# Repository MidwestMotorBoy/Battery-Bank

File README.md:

# Monolith

An ultralight 91 Wh USB-C power bank for backpacking: 4S1P 21700 pack, two bidirectional USB-C PD ports designed for 100 W total, TI CC2340 Bluetooth LE MCU.

## Where the project stands (2026-11-13)

Nothing has been built, assembled or bench-tested yet. Every number in this repo is a design or model value, not a measurement.

- **The design is complete on paper:** schematic, board layout, enclosure model with print files, assembly and bring-up procedures, and a parts tracker for the first five packs.
- **The board is the script-built layout on `master`** (Logan's choice on 2026-11-13; details in [The board layout and its predecessor](#the-board-layout-and-its-predecessor)). It passes DRC and was checked by solver, but it has not been reviewed by a person. Its JLC order files were made on 2026-11-14 ([`ORDER-NOTES.md`](hardware/Production/jlc/ORDER-NOTES.md)). The earlier hand-routed layout, approved on 2026-10-30, is history: its order files, reviews and board-specific studies are kept and labelled as such.
- **The enclosure has been through four drop studies and a thermal study**, the last a full 3D explicit drop model (2026-11-11 and 11-12) that added the rail spines under the board. See [Analysis](#analysis).
- **Next:** review the board in KiCad, fix three silkscreen items and order it, print the first cup (it is the fit test: there are no separate fit coupons), weld a pack, bring the board up, and run the drop and thermal tests that the models can only estimate.

Where to read more:

| | |
|---|---|
| [`docs/spec.md`](docs/spec.md) | The single source of truth for every decision (cells, thresholds, enclosure, firmware policy). Where this README and the spec disagree, the spec wins |
| [`hardware/Production/README.md`](hardware/Production/README.md) | The board's dated change log with the reasoning for each part choice |
| [`docs/analysis/`](docs/analysis/README.md) | Model studies: thermal, drop, bumper materials, switching loops, inner copper |
| [`docs/reviews/`](docs/reviews/README.md) | Board and enclosure reviews, with the full review history |
| [`docs/mechanical-design.md`](docs/mechanical-design.md), [`docs/viewer/`](docs/viewer/README.md) | The enclosure and its interactive 3D viewer |
| [`docs/production/`](docs/production/) | Assembly, spot welding, bring-up and gauge training |
| [`ordering/`](ordering/README.md) | What to buy, from where, and its status |

## Design overview

The goal is a hiking power bank that is lighter and better behaved than the off-the-shelf ones: under the 100 Wh carry-on limit, able to charge or run 20 V USB-C PD loads, with a proper fuel gauge and a phone app. The pack is four BAK N21700CX-65E cells (6.5 Ah, 3.5 V nominal) in 4S1P: 91 Wh typical, spot-welded with pure nickel strip and managed by a TI BQ40Z50-R2 gauge/protector with hardware second-level protection (BQ294700 plus a chemical fuse). Each of the two USB-C ports has its own TPS25751 PD controller and BQ25756 bidirectional buck-boost converter, so either port can charge the pack (including from a 5 V solar panel) or source up to 20 V / 5 A, with the pair thermally limited to 100 W; a TPS62933 buck supplies each port's 5 V source rail and a TPS62177 buck supplies the 3.3 V rail. A CC2340R5MODA Bluetooth LE module runs the charge policy, port power sharing and a custom GATT service for an iPhone app. The electronics live on one 43 × 74 mm 6-layer board along one face of the cells, inside an MJF nylon cup closed on five sides and sealed by a bottom cap with one radial O-ring, with TPU bumpers at both ends. There is no metal enclosure: the power stage sheds its heat into the cells through thermal vias and a gap filler.

| | |
|---|---|
| **Energy** | 91 Wh typical, 88.9 Wh minimum (4S1P, 14.0 V, 6.5 Ah, BAK N21700CX-65E cells), under the 100 Wh carry-on limit |
| **Ports** | 2 × USB-C, each bidirectional PD 5–20 V up to 5 A; 100 W total as a burst, then a linear thermal derate to a sustained ~40 W ([policy](docs/firmware/charge-and-thermal-policy.md)) |
| **Gauge / protection** | BQ40Z50-R2 (Impedance Track, SMBus), Infineon BSC007N04LS6 CHG/DSG FETs, 1 mΩ shunt; BQ294700 + chemical fuse as the independent second level |
| **MCU** | TI CC2340R5MODA (Cortex-M0+ Bluetooth LE module with integrated antenna) |
| **Board** | 43.2 × 74.35 mm, 6 layers, 1.6 mm, 2 oz outer / 0.5 oz inner copper, ENIG, filled and capped vias; JLCPCB assembly of F.Cu, B.Cu parts hand-fitted |
| **Enclosure** | MJF PA12 cup and bottom cap (one radial NBR O-ring), PA12 cell carrier and board rails, TPU 95A bumpers; 60.9 × 52.7 × 95.5 mm, about 402.2 g (modelled); IP67 is the target |
| **Tools** | KiCad 10 with Python scripts, TI SimpleLink Low Power F3 SDK, Xcode (app on the `app` branch) |

## Status

**Done**

- **Schematic:** six sheets, 289 footprints. Derived by script from an earlier bench design that went through four schematic reviews, with a netlist check that every surviving pin kept its net. Loss cuts, the BAK 65E cell change, the late part swaps (TVS2200 clone, KEMET T593V bulk caps, 2.0 mm inductors) and the UART_TX debug pin are in. ERC is clean (0 errors).
- **Board layout:** the script-built layout of 2026-11-10 (PR #66, commit `dd34285`), placed and routed by script into the outline the enclosure gives, DRC clean, and ahead of or level with the earlier hand-routed layout on loop inductance, copper loss and via current in the solver comparison. Logan made it the design on 2026-11-13. A whole-project pre-order review on 2026-11-07 found no wiring error in the schematic it implements.
- **Earlier hand-routed layout (history):** placed 2026-10-28, routed and reviewed revision by revision up to rev 12 on 2026-10-30, approved the same day (PR #44). It is the board file at commit `8dd9eb6`; its order files are in [`hardware/Production/retired/jlc-hand-routed/`](hardware/Production/retired/jlc-hand-routed/ORDER-NOTES.md).
- **Mechanical:** parametric cup enclosure with 129 clearance, seal, sealed-pressure and drop load-path checks, all passing, STL print files by material, STEP export and an interactive viewer ([`docs/mechanical-design.md`](docs/mechanical-design.md)). The cup carries the drop loads since 2026-11-03 (edge lands, lips, cradles, spacers) and props the board at mid-span since 2026-11-11 (rail spines).
- **Analysis:** thermal with both ports loaded, four drop studies ending in a full 3D explicit model, a bumper materials study, the inductance of every switching loop, and an inner copper weight study ([Analysis](#analysis)).
- **Cells and pack build:** BAK N21700CX-65E, BSC007N04LS6 protection FETs sized for its short-circuit current ([options](research_notes/protection-fets/options.md)), P20B spot welding with 0.2 × 10 mm pure nickel and wire PACK tails ([welding](docs/production/spot-welding.md), [assembly](docs/production/p0-assembly.md)), Parker GEL 30 gap filler, front-cell NTCs as SMD parts on the board under the gap filler (TH101 / TH104).
- **Firmware policy:** charge current and discharge power as linear ramps on the hottest cell temperature ([policy](docs/firmware/charge-and-thermal-policy.md)); a LaunchPad build of the firmware skeleton and TI's `basic_ble` runs.
- **Ordering:** every part for five packs is in [`ordering/parts-tracker.csv`](ordering/README.md). The two parts LCSC does not stock (TPS25751D, SiZ240DT) were pre-ordered at JLC on 2026-11-07.

**Remaining**

- Review the board in KiCad: it has been checked by DRC, script and solver only.
- Fix the silkscreen items in [`ORDER-NOTES.md`](hardware/Production/jlc/ORDER-NOTES.md) (the title text is off the board edge), rerun `hardware/Production/jlc/make_package.sh` after any board change, and go through the checkout checks there.
- Rerun the board-specific studies for this layout where the margin is small: the 3D drop model (of the four capacitors with the smallest wall margins, three moved by 5 to 13 mm and the fourth turned 90°) and the thermal runs.
- Order the board and the printed parts. The first real cup, cap and core are the fit test.
- Weld the pack, bring up the board and train the gauge ([`docs/production/p0-bringup-and-training.md`](docs/production/p0-bringup-and-training.md)).
- Firmware beyond the skeleton: the P0 pin map, gauge and PD-controller drivers, the TPS25751 patch bundle and its loader, charge policy, power sharing, BLE GATT, MCUboot OTA.
- Tests the models cannot replace: a witness-paint drop test on the first print, the 100 W thermal test, an IP67 dunk test, label ratings.
- Thermal rerun with the 1.6 mm cup walls and the rail spines (the spines take about 12 % of the gap filler's conductance; the thermal study predates them).
- iPhone app (SwiftUI + CoreBluetooth).

## Hardware

### The KiCad project

Everything for the board is in [`hardware/Production/`](hardware/Production/), KiCad 10. The symbol library, footprint library and 3D models are project-local, so the project opens with no extra setup.

| File | What it is |
|---|---|
| `Monolith.kicad_pro` | The project; open this |
| `Monolith.kicad_pcb` | The 6-layer board: the script-built layout (commit `dd34285`). The earlier hand-routed layout is the same file at commit `8dd9eb6` (see below) |
| `Monolith.kicad_sch` | Root sheet. Sub-sheets: `gauge.kicad_sch` (Cells and Gauge), `power.kicad_sch` (3V3 Rail), `mcu.kicad_sch` (MCU), and `usb_port.kicad_sch` used twice (USB Port 1, USB Port 2) |
| `MonolithDev.kicad_sym`, `MonolithDev.pretty/`, `3dmodels/` | Project-local symbol library, footprints and STEP models (wired up by `sym-lib-table` / `fp-lib-table`) |
| `Monolith.kicad_dru` | Custom DRC rules (net-class clearances, keep-outs) |
| `jlc/` | [`ORDER-NOTES.md`](hardware/Production/jlc/ORDER-NOTES.md): the JLCPCB order package for this board (gerber zip, BOM, CPL, hand-solder list, made 2026-11-14 by `make_package.sh`), the PCB options and the checkout checks |
| `retired/jlc-hand-routed/` | History: the complete order package of the hand-routed layout (gerber zip, BOM, CPL, hand-solder list). Not for today's board |
| `tools/` | Python scripts that generated the schematic, stack-up, outline and mechanical keep-outs from the enclosure model ([table](hardware/Production/README.md#tools)) |
| `groundup/` | The tools, passes and solver comparison behind the script-built layout ("ground-up" in that folder's notes; [README](hardware/Production/groundup/README.md)) |
| `README.md` | Dated change log: every part choice and change with its reasoning |

The board outline, peg holes, wire holes and keep-outs come from the enclosure model (`hardware/mechanical/monolith_shell.py`) through `tools/make_board.py`, so mechanical changes go there first. Reference designators follow the sheets: 1xx cells and gauge, 2xx 3V3 rail, 3xx MCU, 4xx port 1, 5xx port 2.

### The board layout and its predecessor

Two layouts of the same schematic exist. On 2026-11-13 Logan chose the script-built one as the design. Both use the same outline, holes, USB-C connectors, wire pads, NTCs, antenna module, bottom-side parts and main inductors, so both fit the same cup; 246 of the 289 footprints have a different position or rotation (234 moved by more than 0.1 mm).

| | Script-built board (the design) | Hand-routed board (history) |
|---|---|---|
| **Where** | `Monolith.kicad_pcb` on `master` (commit `dd34285`, PR #66, 2026-11-10) | `Monolith.kicad_pcb` at commit `8dd9eb6` |
| **How it was made** | Placed and routed by script from the schematic, with a DC and loop-inductance solver in the loop, in two fix passes ([`groundup/`](hardware/Production/groundup/README.md)) | Placed and routed by hand in KiCad |
| **Review** | DRC clean (0 errors, 0 unconnected); compared by solver against the hand-routed board ([`groundup/compare/`](hardware/Production/groundup/compare/README.md)); **not yet reviewed by a person** | Reviewed revision by revision up to rev 12 and a final blocker review on 2026-10-30, approved (PR #44) |
| **Solver comparison (model values)** | Charger hot loops 0.50 to 0.56 nH; gate loops 44 nH in sum; copper loss at 100 W 435 / 358 mW (port 1 / port 2); 5.3 / 5.7 min at 100 W before the derate; 258 mm of signal track in a ground plane | 0.54 to 0.67 nH; 49 nH; 469 / 415 mW; 5.0 / 5.3 min; 34 mm |
| **Order files** | None yet. Gerbers, BOM and CPL are made together after the review ([`jlc/ORDER-NOTES.md`](hardware/Production/jlc/ORDER-NOTES.md)) | Complete set, kept in [`retired/jlc-hand-routed/`](hardware/Production/retired/jlc-hand-routed/ORDER-NOTES.md) |
| **Renders, plots, mechanical board data** | Regenerated from this board on 2026-11-13; all 129 enclosure checks pass with its part positions | In git history (pictures at `401b2ee` and earlier; part meshes kept as `hardware/mechanical/board/monolith_board_handrouted.npz`) |
| **Reviews and studies** | The solver comparison only. The drop and thermal studies have not been rerun for its part positions | Every board review in [`docs/reviews/`](docs/reviews/README.md) and every study in [`docs/analysis/`](docs/analysis/README.md) used this board |

As of 2026-11-13, open PR #68 holds a cleaned-up version of the script-built board (a tidiness pass on 2026-11-11) and would replace the board file on `master` if merged; the pictures can be made again with [`docs/hardware/board_pictures.py`](docs/hardware/board_pictures.py). Never mix files between the two layouts: gerbers made from the board on `master` with the CPL in `retired/jlc-hand-routed/` would place almost every part in the wrong spot.

### Schematics, renders and plots

- [`docs/hardware/monolith-p0-schematic.pdf`](docs/hardware/monolith-p0-schematic.pdf): all six sheets, exported from the current schematic on 2026-11-13. It is the same for both layouts.
- [`docs/hardware/monolith-p0-layers.pdf`](docs/hardware/monolith-p0-layers.pdf): the script-built board, front and back (copper, mask, silk), then every copper layer (F.Cu, In1–In4, B.Cu), one page each, plotted on 2026-11-13 from master's board (`dd34285`).
- A 3D STEP of the whole assembly can be generated with `hardware/mechanical/monolith_step.py`.

#### The board

Raytraced in KiCad 10 (`kicad-cli pcb render`, all 3D models) on 2026-11-13 from the board on `master` (`dd34285`) by [`docs/hardware/board_pictures.py`](docs/hardware/board_pictures.py), which also writes the plots and the layers PDF.

<p align="center"></p>

| Top (F.Cu side, faces the cup wall) | Bottom (B.Cu side, faces the cells) |
|---|---|
|  |  |

<p align="center"></p>

#### Board plots

| Front (F.Cu, mask, silk) | Back (B.Cu, mask, silk, mirrored) |
|---|---|
|  |  |

The USB-C ports are at the top edge of the plots (the right edge of the flat renders), the cell wire holes (PACK−, PACK+ and the Kelvin senses) at the bottom tab, and the two power stages fill the middle: USB1's stage (L401) toward +y and USB2's (L501) toward −y. The bare copper boxes on the back are the gap-filler pads that couple the stages to the cells.

### Per port

- TPS25751D USB-C PD controller, configured from its own M24512 EEPROM (patch-bundle programming notes in [`docs/firmware/tps25751-eeprom-programming.md`](docs/firmware/tps25751-eeprom-programming.md)).
- BQ25756 bidirectional buck-boost, 5 mΩ sense resistors, two SiZ240DT 40 V half-bridges, Coilcraft XGL7030-332 3.3 µH at 500 kHz, and a 9 V gate-drive LDO (TPS7A4101), off by default and enabled through the TPS25751's GPIO6 when the pack is above 10 V. Gate resistors fitted as 0 Ω links with DNP RC snubbers so ringing can be fixed without a respin.
- TPS62933 5 V buck for the port's 5 V source rail; TPD6S300 CC protection (24 V short-to-VBUS, IEC ESD); TVS2200 flat clamp on VBUS.
- Shou Han IP68 right-angle USB-C receptacle, 5 A / 20 V.

### Pack and supervision

- BQ40Z50-R2 with four cell NTCs (the two front ones are SMD parts on the board, TH101 / TH104; the back two are wired to their cans), cell balancing and JEITA; BSC007N04LS6 CHG/DSG FETs; 1 mΩ shunt; BQ294700 per-cell OVP that fires the WSFB1514 chemical fuse independently of the gauge.
- One wire-ORed interrupt line (both PD controllers, gauge BTP) into the MCU; CHG_INH pulled up so a reset, hang or unprogrammed MCU stops charging.
- Idle current about 400 µA (estimate, [budget](docs/devboard/power-budget.md)), with a gauge ship mode for storage.

Datasheets and app notes the design was checked against are in `datasheets/`: [`datasheets/README.md`](datasheets/README.md) maps each file to its part.

### Earlier bench design

`hardware/DevBoard/` and `docs/devboard/` hold the bench "dev board" (rev A8) that P0 was derived from: its four schematic reviews, circuit description and budgets. It was never ordered (P0 is the first build since 2026-10-18) and is kept only as the reviewed reference and history.

## Enclosure

The enclosure is a parametric Python model in [`hardware/mechanical/`](hardware/mechanical/) (`monolith_shell.py`, `monolith_parts.py`, `monolith_cup.py`). The model runs its own 129 checks (clearances against the board's part meshes, an insertion sweep, seal squeeze, sealed pressure, drop load-path gaps and bearing stresses) and writes the print files, the pictures in this README and the viewer. [`docs/mechanical-design.md`](docs/mechanical-design.md) describes the design and its checks.

- **Printed parts:** cup, bottom cap, cell carrier, two board rails and four post spacers in MJF PA12; top and bottom bumpers (one piece each, 30 % gyroid slabs) and the cap pad in FDM TPU 95A. Print files by material: [`hardware/mechanical/stl/`](hardware/mechanical/stl/README.md).
- **Sealing:** one 58 × 54 × 2 mm NBR O-ring between cup and cap, the two USB-C receptacles' own seal rings in the cup's bores, and a 12 mm ePTFE vent patch on the cap under the bottom bumper.
- **What holds the core:** the cup carries the loads. Edge lands and lips hold the board's long edges, cradles hold the front cells, the rails ride on the front cans and prop the board at mid-span with a spine across the gap-filler zone, and the cap's feet and overtravel posts catch the core in a cap-end drop.
- **Interactive 3D viewer:** [`docs/viewer/`](docs/viewer/README.md) (parts on and off, section cuts).
- **Assembly:** [`docs/production/p0-assembly.md`](docs/production/p0-assembly.md), with the step pictures in `hardware/mechanical/assembly_steps/`.
- **Label:** the wrap label artwork and print file are in [`hardware/label/`](hardware/label/README.md).

## Analysis

Model studies of the whole pack, each in its own folder under [`docs/analysis/`](docs/analysis/README.md) with the scripts, the numbers as JSON and every figure. Every study was run on the earlier hand-routed board (its copper and its part positions) and the cup as it was on the study's date; none has been rerun for the script-built board that is now the design. The enclosure findings carry over, because the cup, the outline and the parts the cup keys on are the same. The board-specific numbers (copper loss, loop inductance, the parts next to the rail spines in the drop model) describe the hand-routed layout; where the solver comparison in [`groundup/compare/`](hardware/Production/groundup/compare/README.md) has the same number for the script-built board, it is given. Each README opens with a status block that says which geometry it ran on and what became of each finding. Every number is a model value until the bench tests.

| Study | Date | What it answered |
|---|---|---|
| [Thermal, 25 W + 20 W](#thermal-usb1-at-25-w-and-usb2-at-20-w-together) | 2026-10-31 | Both ports loaded from full to empty at 25, 35 and 40 °C |
| [Drop, six poses](#drop-1-m-onto-concrete) | 2026-10-31 | First 1 m drop model; three housing fixes |
| [Bumper materials](#bumper-materials-and-structure) | 2026-11-01, 11-05 | Elastic resins and engineered slabs against FDM TPU |
| [Drop with part-to-part contact](#drop-1-m-onto-concrete) | 2026-11-04, 11-05 | Loads and stress in every part; cup fixes |
| [Inner copper weight](#inner-copper-weight) | 2026-11-05 | 0.5, 1 or 2 oz inner layers |
| [Switching loops](#switching-loop-inductance) | 2026-11-06 | Inductance and ringing of every hot loop and gate loop |
| [Drop in 3D](#drop-1-m-onto-concrete) | 2026-11-11, 11-12 | Full explicit model of the back-face drop; rail spines |

### Thermal: USB1 at 25 W and USB2 at 20 W together

[`docs/analysis/2026-10-31-thermal-25w-20w/`](docs/analysis/2026-10-31-thermal-25w-20w/README.md). Both ports deliver from full to empty (45 W, USB1 at 15 V, USB2 at 9 V) in the 3D pack model ([`research_notes/Pack thermal BAK 65E/`](research_notes/Pack%20thermal%20BAK%2065E/README.md)) with the hand-routed board's copper losses and the firmware derate in the loop.

- **At 25 °C** the pack runs the whole battery at 45 W (118 min, 88.4 Wh) and cuts to 40 W only for the last 3 minutes. The hottest board part peaks at 51 °C, the hottest point in any cell at 45.7 °C, the outside at 46.6 °C.
- **At 35 °C** the derate starts at 20 min and settles at 30 W (USB1 down to 10 W, USB2 kept at 20 W); the hottest part reaches 56 °C and the cells 51 °C. At 40 °C USB1 is cut to 0 W for most of the run.
- **Heat** at 45 W is 2.4 W: 0.8 W in the USB1 stage, 1.0 W in the USB2 stage, 0.5 W in the cells. The 6-layer board keeps itself within 3.6 K end to end.
- Even with the derate switched off at 35 °C (a firmware failure) the cells stop at 55.4 °C, under their 60 °C discharge limit.
- **Not rerun since.** The model's cup has 1.2 mm side walls and no rail spines. The cup now has 1.6 mm walls, and the spines cross the gap-filler zone and take about 12 % of its conductance, so these temperatures are probably slightly optimistic. The copper losses are the hand-routed board's. For the script-built board only the 100 W burst was run, in the solver comparison: 5.3 / 5.7 min before the derate (port 1 / port 2) against 5.0 / 5.3, with the hottest part at 58.1 / 58.9 °C against 59.4 / 60.2 °C.

<p align="center"><sub>The board under the temperatures above is the <b>hand-routed</b> board this study ran on (silk "REV 1.0 10/30/26"), not the script-built board on <code>master</code>. For the current board see <a href="#the-board">The board</a>.</sub></p>

### Inner copper weight

[`docs/analysis/2026-11-05-inner-copper/`](docs/analysis/2026-11-05-inner-copper/README.md). The board is specified with 2 oz outer and 0.5 oz inner copper. This study solved the hand-routed board's power-path resistance and reran the 100 W burst with 1 oz and 2 oz inner layers. The script-built board has the same stack-up; the study has not been repeated on its copper.

| Inner copper | Path resistance, port 1 / port 2 | Port 1 copper loss at 100 W | Minutes at 100 W before the derate, port 1 / port 2 | Hottest part, port 1 / port 2 |
|---|---|---|---|---|
| 0.5 oz (as specified) | 8.63 / 7.50 mΩ | 0.29 W | 5.0 / 5.33 | 59.4 / 60.2 °C |
| 1 oz | 6.95 / 5.75 mΩ | 0.24 W | 5.33 / 5.67 | 57.2 / 57.9 °C |
| 2 oz | 5.96 / 4.68 mΩ | 0.20 W | 5.83 / 6.0 | 54.9 / 55.3 °C |

The gain is almost all heat spreading, not lower I²R: the outer layers carry the high-current copper already. The extra mass is about 1.4 g at 1 oz and about 4 g at 2 oz. 1 oz inner was recommended if JLC's price difference is small; it has not been decided, and the board stays 2 oz / 0.5 oz until it is.

### Drop: 1 m onto concrete

Three models of increasing depth, each built because the one before could not answer the next question. All are for a 1 m drop at 4.43 m/s onto a rigid floor.

1. **Six poses, lumped** ([`2026-10-31-drop-1m/`](docs/analysis/2026-10-31-drop-1m/README.md)). The bumpers' crush law, a finite-element stiffness of the cup and its contents, and a plate model of the board, for a flat drop on each end, the board face, a narrow side, and a corner at each end. It found the 20 % gyroid port-end slab bottoming out (2685 g on the cells and board) and led to three fixes (PR #50): the bumper slabs at **30 % gyroid**, the two M2 screw heads **counterbored 0.8 mm** so they sit below the bumper band, and **pockets in the board-face wall** over the two inductors.
2. **Contact between every moving part** ([`2026-11-04-drop-stress/`](docs/analysis/2026-11-04-drop-stress/README.md)). Each moving part is its own body with contacts to its neighbours, finite-element compliance and stress per part, and the board as a plate on one-sided supports. It gives part loads and stresses for the five flat drops (edges and corners are not usable in this model). It led to the 2026-11-05 cup fixes (PR #64): bottom rail tongues set back, larger cap overtravel posts plus a fifth, and cradle reliefs under two bulk capacitors. It also showed about 8,000 µε in the board in the back-face and board-face drops, which is what the 3D study took up.
3. **Full 3D explicit model of the back-face drop** ([`2026-11-11-drop-3d/`](docs/analysis/2026-11-11-drop-3d/README.md)). OpenCourant, about 900k nodes, quadratic tetrahedra for the nylon and TPU parts, for the worst pose of the lumped studies: flat onto the back (cell) face, where the board's own inertia bends it toward the cells and then swings it into the board-face wall on the rebound. On the cup as it was before this study the board bent across its middle (about 5,000 µε in a full-width band) and the rebound pushed several F.Cu capacitors and inductors into the wall. The fixes (PR #69): **rail spines** that prop the board at mid-span (one clip-on rail per side, its bottom and top blocks joined across the gap-filler zone), ribs on the cup under the board's long edges, 1.5 mm of travel past the bottom rail tongue tips so the rails ride on the front cans, and 0.7 mm inductor pockets. Run 9 checked the merged geometry: board strain 3,089 µε at the 99th percentile and 4,022 µε peak, no F.Cu part reaches the wall, and the tongue tips stop 0.12 mm short. The cap overtravel posts yielded at their sharp top rims, so their tops now have a 0.3 mm chamfer (PR #70, not rerun).

Where each pose stands today, from the newest model that covers it:

| Pose | Newest result | State |
|---|---|---|
| Flat on the port end | 572 g on the cells and board, slab crush 2.6 of 6 mm (lumped, 30 % slab); every part under 7 MPa (contact model) | Fixed by the 30 % slab |
| Flat on the cap end | 1182 g (lumped); overtravel posts 42 MPa, was 107 MPa (contact model) | Open: about 280 N on each bottom rail tongue, and about 1.15 kN on the two M2 screws in the rebound (a lumped estimate) |
| Flat on the back (cell) face | Board 3,089 µε p99, 4,022 µε peak; closest F.Cu part 0.02 mm from the wall (3D, run 9) | Mid-span bending fixed by the rail spines. Open: about 4,000 µε on the board's long edges where the spines end, local yield in the carrier webs, and capacitor margins below the model's resolution |
| Flat on the board face | Board 7,800 µε p99, C434 / C531 0.06 mm from the wall (contact model) | Open. Not rerun since the rail spines and not run in 3D |
| Flat on a narrow side | 4013 g (lumped); cup wall 178 MPa and cradles 143 MPa on a coarse mesh (contact model) | Open: the bottom bumper band is only 1 mm of solid TPU on this side |
| Corners | 2611 g port end, 1550 g cap end (lumped) | No usable stress result in any of the three models |

The lumped g values are from the 2026-10-31 rerun on the 399.6 g cup, before the lands, cradles and spines were added; they have not been rerun on today's 402.2 g cup. The gap filler is carried as mass only: a sensitivity bracket in the contact study suggests it could cut the back-face strain by about 18 % but could also drag parts toward the wall on the rebound. A **witness-paint drop test on the first print** is the planned check for the open items.

The part names and part-to-wall gaps in this table are for the hand-routed board. The script-built board keeps the parts the cup keys on (L401 / L501, the bulk capacitors, the NTCs, the USB-C connectors, the antenna module, the holes), and it passes the model's static clearance checks, but the four capacitors with the smallest margins are not where the studies had them: C434 and C524 moved about 13 mm and C420 about 5 mm; C531 moved 0.4 mm and turned 90°. The margins of 0.02 to 0.06 mm therefore say nothing about the new layout until the contact and 3D models are rerun with its part positions.

### Bumper materials and structure

[`docs/analysis/2026-11-01-bumper-materials/`](docs/analysis/2026-11-01-bumper-materials/README.md). The 2026-10-31 drop model rerun with other materials and slab structures. Analysis only: the design keeps FDM TPU 95A bumpers with 30 % gyroid slabs.

- **Formlabs elastic resins** in the same 6 mm port-end slab give 1,888 to 3,362 g against 572 g for the TPU slab. Flexible 80A V2 needs a 10 mm slab to match, and Flexible 50A never gets below about 1,270 g.
- **PEBA 85A** (studied on 2026-10-31, in the drop study's folder) is 10 to 20 % gentler in the bands but bottoms out worse at the port end, so TPU stays.
- **An engineered slab** does better than a softer material: a vertical-wall honeycomb in TPU 95A at 15 to 17 % gives 397 to 557 g at 1 m with about half the slab mass of today's gyroid (4.6 to 5.3 g against 9.3 g). It has not been adopted in the model.
- **A Flexible 50A cap pad** would hold its preload after heat far better than TPU (compression set 3.1 % against 90 % at 70 °C). It is an idea only.

### Switching-loop inductance

[`docs/analysis/2026-11-06-loop-area/`](docs/analysis/2026-11-06-loop-area/README.md). A 3D partial-inductance solve on the hand-routed board's real copper for every hot loop (the four BQ25756 half-bridge legs, the two 5 V bucks, the 3V3 buck) and the eight gate-drive loops, with ringing estimates.

- **Hot loops:** 0.53 to 0.66 nH on the BQ25756 legs, 0.54 and 0.60 nH on the 5 V bucks, 1.39 nH on the 3V3 buck. The 0402 capacitor next to each FET carries 58 to 68 % of the edge current.
- **Ringing:** the BQ25756 switch nodes ring at about 395 to 425 MHz with an expected peak of 18.8 to 22.4 V; the worst-case bound with an instant edge is 32 to 33 V against the FETs' 40 V rating.
- **Gate loops:** 2.9 to 9.2 nH. The tightest margin is the low-side Miller bounce, about 0.46 V against a 1.1 V minimum threshold.
- **No loop needs a fix.** Two optional tweaks are listed in the study. These numbers are for the hand-routed board.
- **Script-built board:** the same solver steered and checked the new layout ([`groundup/compare/`](hardware/Production/groundup/compare/README.md)). Its four charger hot loops are 0.50 to 0.56 nH, the three small bucks 0.30 to 1.22 nH, and the eight gate loops 3.3 to 8.0 nH, 44 nH in sum. That comparison re-solved the hand-routed board with its own ground setting and got 0.54 to 0.67 nH, 0.53 to 1.40 nH and 49 nH in sum, so compare within one run, not across the two. The ringing estimates were not redone for the script-built board.

### Reviews

Board and enclosure reviews are in [`docs/reviews/`](docs/reviews/README.md), with a table of the whole review history. The board-layout reviews are history: they reviewed the hand-routed layout, and the script-built board has had no review by a person yet. The routed-board review of 2026-10-30 has the copper resistance of every power path and the current-sense tap checks of that layout (its fix list was closed in the later revisions that day), and its solver tools are the ones the script-built layout was checked with. The schematic findings of the reviews apply to both layouts. The mouth-band review (2026-10-31) and the rail-retention review (2026-11-03) are the enclosure decisions behind the thick cup mouth and the cup-carried drop loads.

## Firmware

`firmware/` targets the CC2340R5MODA with TI's SimpleLink Low Power F3 SDK. Until a board exists it runs on the LP-EM-CC2340R53 LaunchPad, which has the same silicon and memory. The firmware has not changed since 2026-10-29.

- **Toolchain:** TI Arm Clang 5.1.1.LTS, SysConfig 1.26.4 and `gmake` from Code Composer Studio 21.0.1, the LPF3 SDK 9.23.00.27, and UniFlash 9.7.0 / DSLite with an XDS110 probe. Everything is driven from a `Makefile`; install steps and version pins are in [`firmware/README.md`](firmware/README.md).
- **Structure:** `boards/<board>.syscfg` holds the pin map and CCFG per target (P0's is still to write); SysConfig generates the driver configuration into `build/<board>/syscfg/`; `app/` is the application. NoRTOS for bring-up, moving to FreeRTOS when the BLE stack comes in.
- **State:** the skeleton (banner and reset reason on UART, heartbeat LED, a button standing in for the IRQ line) and TI's `basic_ble` (in `ble/`) build and run on the LaunchPad.
- **Planned:** the P0 board file `boards/p0.syscfg`, the TPS25751 patch bundle with a host-side I2C loader (needed before bring-up), SMBus gauge driver, TPS25751 4CC commands, the [charge and thermal policy](docs/firmware/charge-and-thermal-policy.md) with a once-a-second readback of the charger's limits, port power sharing, settings in flash, BLE GATT service, MCUboot signed OTA. The full list is in the spec.

## Repo layout

```
.
├── README.md
├── LICENSE
├── .claude/skills/        Electrical design techniques from this project as skills for AI agents (index: README.md)
├── hardware/
│   ├── Production/        KiCad 10 project "Monolith" (P0): schematic, board, libraries, order notes, generator scripts, the layout tools (groundup/), retired order files
│   ├── mechanical/        Enclosure model (Python → STL/STEP/DXF), print files by material, renders
│   ├── label/             Wrap label for the cup
│   └── DevBoard/          Earlier bench design, never built (reference only)
├── docs/
│   ├── spec.md            The current design spec: the single source of truth
│   ├── analysis/          Model studies: thermal, three drop models, bumper materials, switching loops, inner copper
│   ├── reviews/           Board and enclosure reviews with figures, and the review history
│   ├── hardware/          Schematic and layer PDFs, renders and board plots exported from KiCad
│   ├── production/        P0 assembly (the cup), spot welding, bring-up and gauge training
│   ├── firmware/          Charge and thermal policy, TPS25751 EEPROM programming
│   ├── mechanical-design.md
│   ├── viewer/            Interactive 3D viewer of the pack (one HTML file)
│   ├── devboard/          Bench design record (reviews 1–4, budgets, simulations), history
│   └── archive/           Superseded notes, kept for history
├── firmware/              CC2340 firmware: Makefile, boards/*.syscfg, app/, ble/
├── ordering/              Parts tracker for the first five packs (CSV is the source, README is generated)
├── datasheets/            Manufacturer datasheets and app notes (README.md is the index)
├── reports/               Research reports (potting and drop protection; the 2026-10-21 enclosure concept study that led to the cup)
├── research_notes/        Working notes and models: pack thermal model (BAK 65E), loss reduction, protection FETs, enclosure concepts
└── tools/                 fetch_datasheets.sh
```

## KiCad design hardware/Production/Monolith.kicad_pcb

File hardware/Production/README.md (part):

# Monolith production board

KiCad 10 project `Monolith`: the P0 board. The schematic (`Monolith.kicad_sch` with the sheets `gauge`, `power` (3V3 Rail), `mcu` and `usb_port`, the last used once per port; 301 references) is the design of record.

**Which board is which (2026-11-13).**

- **The design is the script-built board**: `Monolith.kicad_pcb` on `master` (commit `dd34285`), by Logan's decision of 2026-11-13. It is the ground-up re-layout that was merged in PR #66 on 2026-11-10. It keeps the schematic, outline, holes, USB-C connectors, wire pads, NTCs, antenna module, the 12 B.Cu parts and L401/L501 of the hand-routed board; every other part was placed again and all copper was drawn again. It passes DRC (0 errors, 0 unconnected) and was checked by script and solver, but nobody has reviewed it in KiCad. Details: [`groundup/README.md`](groundup/README.md).
- **The hand-routed board is history.** Logan approved it on 2026-10-30 (PR #44) and added silk labels, the UART_TX route and F.Cu corner fills on 2026-11-08. It is the same file at commit `8dd9eb6`: `git show 8dd9eb6:hardware/Production/Monolith.kicad_pcb`. Its order package (gerber zip, BOM, CPL) moved to [`retired/jlc-hand-routed/`](retired/jlc-hand-routed/ORDER-NOTES.md) on 2026-11-13 and must not be used with today's board. The reviews in `docs/reviews/` and the board-specific numbers of the studies in `docs/analysis/` are for this board. The dated entries below up to 2026-11-08 describe work on it.
- **Redone for the script-built board on 2026-11-13:** the renders, plots and layers PDF in `docs/hardware/` (`docs/hardware/board_pictures.py`), the mechanical model's board data (`hardware/mechanical/board/monolith_board.npz`, all 129 enclosure checks pass), the model pictures, the viewer and the STEP set.
- **Not yet done for it:** a review in KiCad. The order package was made on 2026-11-14 ([`jlc/ORDER-NOTES.md`](jlc/ORDER-NOTES.md); `jlc/make_package.sh` remakes it, with the hand-made BOM and rotation fixes, after any change). The drop and thermal studies have not been rerun for its part positions and copper.
- **Seen while making the pictures on 2026-11-13, for the review (the board file was not touched):** the F.SilkS title text (`Monolith Bat Bank / REV 1.0 / 10/30/26`) is anchored at (121.5, 136.5) and left-justified, so it starts 0.1 mm from the board edge, runs off the board and will not print; the `T3` and `T3R` wire-hole labels overlap each other at J119 / J120; the B.SilkS gap-filler text still says `GEL 30  2.3 g` (the amount is 1.9 g per zone since the rail spines).
- Open PR #68 (branch `claude/project-thread-ploune`, not merged) holds a cleaned-up version of the script-built board (cleanup pass of 2026-11-11). Merging it replaces the board file on `master`; rerun `docs/hardware/board_pictures.py` and `hardware/mechanical/board/board_from_step.py` after that.
- No board has been ordered or built (two parts, TPS25751D and SiZ240DT, were pre-ordered at JLC on 2026-11-07).

The dev board was skipped on 2026-10-18, so P0 is the first build (gauge training and the dev board checks happen on P0: `docs/production/p0-bringup-and-training.md`). The schematic is the dev board's (rev A8) with the dev-only parts removed, plus the P0 changes below.

The current design is in `docs/spec.md`, which wins where this file disagrees. The sections below are a dated design log: the newest entries (2026-10-28 to 2026-11-10) come right after the tools table, the older ones follow. Sections that a later decision replaced say so and are kept as history. In short, as of 2026-11-13:

- **Cells:** four BAK N21700CX-65E (6500 mAh) in 4S1P, 14.0 V nominal, 91 Wh (since 2026-10-23; the FEB 21700G section below is history).
- **Enclosure:** the MJF PA12 cup, vented by a 12 mm ePTFE patch on the cap since 2026-10-31 (no hole in the cup or label; the side tray, its aluminium cover and the top-cap tube are retired; their outputs were removed on 2026-10-29 and are in git history at `5cf521e`).
- **Loss cuts:** Q101/Q102 BSC007N04LS6, a 9 V gate drive per port (U406/U506), L401/L501 XGL7030-332 at 500 kHz.
- **Late part swaps:** L402/L502 ABC EHE05023R3MFB (2.0 mm, since 2026-10-30), D401/D501 Maxinmicro TVS2200DRVR C55616459 and C421/C456/C521/C556 KEMET T593V686M035APE070 (both 2026-10-31).
- **Front-cell NTCs:** SMD TH101 / TH104 on B.Cu (since 2026-10-28; they replace the J102 / J107 wire pads). The back-cell NTC wires go to J117–J120 (since 2026-10-30; they replace J105 / J106).
- **Charge ceiling:** R413/R513 stay 11.8k (decided 2026-11-07, replacing the 2026-10-23 plan for 0 Ω) with `EN_ICHG_PIN = 0`, so firmware sets the limit and the pin is only the no-host fallback.

## Tools

All in `tools/`. Run them from the repo root as `hardware/Production/tools/<name>.py`, with KiCad's Python unless the script's docstring says any Python 3 will do.

| Script | What it does | Status (2026-11-13) |
|---|---|---|
| `make_production.py` | Builds the production schematic from the dev board's (see below); holds the part swaps (`DOWNSIZE`, loss cuts, P0 pads) | Record of how P0 was derived. It overwrites the sheets, which have been edited since 2026-10-28 (J117–J120, UART_TX, the R413/R513 note, the TVS and L402/L502 swaps), so don't re-run it |
| `tidy_production.py`, `layout_production.py` | Drawing tidy and block layout after `make_production.py` (no electrical change) | Record; they edit the sheets in place |
| `check_netlist.py` | Compares the production netlist with the dev board's | Record of the 2026-10-17 to 2026-10-28 derivation; it checks the schematic against the dev board, not against either board file |
| `schlib.py` | Schematic text helpers used by the three above | Helper library |
| `siz240dt.py`, `tpd6s300.py`, `tps7a4101.py` | Symbol, footprint and wiring for the SiZ240DT, TPD6S300 and TPS7A4101 (imported by `make_production.py`) | Record; the footprints and symbols they made are in `MonolithDev.pretty` and `MonolithDev.kicad_sym` |
| `make_board.py` | Board stack-up and outline (from `hardware/mechanical/monolith_shell.py`, the source of the live outline `hardware/mechanical/monolith_side_pcb.dxf`); `--mech` places and locks the wire holes, peg holes and front-cell NTCs; `--keepouts` redraws the `KO_*` rule areas (board closed in KiCad) | `--mech` and `--keepouts` still work on either board but rewrite `Monolith.kicad_pcb`: only at Logan's request. A plain run or `--force` is a record of how the board was started (2026-10-17) |
| `make_3d_models.py`, `step_mesh.py` | Writes the STEP models in `3dmodels/` (pure Python); the SiZ240DT and TPD6S300 models start from the EasyEDA meshes in `3dmodels/source/`, so keep those | Usable; `--board` also writes the model paths into `Monolith.kicad_pcb` (only at Logan's request) |
| `pack_bus_sims.py`, `low_profile_sims.py` | Bulk-capacitor studies (reuse `hardware/DevBoard/tools/cap_sims.py`) | Usable; `low_profile_sims.py` overwrites `hardware/DevBoard/tools/cap_sims.json`, so restore that file from git afterwards |
| `jlc.py`, `jlc_datasheet.py` | JLC part search, and a datasheet download through a part's JLC page | Usable (any Python 3) |

The ground-up re-layout has its own scripts (placement, router, copper, solvers) in [`groundup/`](groundup/README.md) and [`groundup/compare/`](groundup/compare/README.md).

## Ground-up re-layout on master (2026-11-10)

Logan asked on 2026-11-09 for a ground-up, script-built layout that drops into the current cup. It was built on branch `claude/project-thread-ploune` (first version `6aaa778`, fix passes `ffb0dde` and `dd34285`) and merged to `master` in PR #66 on 2026-11-10. Logan then chose to keep it on `master`, so `Monolith.kicad_pcb` is the ground-up board from that date and the approved hand-routed board is the file at `8dd9eb6`.

- **Kept from the hand-routed board:** schematic, project file and design rules, stack-up, outline, peg and wire holes, USB-C connectors, NTCs, U301, the 12 B.Cu parts, L401/L501 and the `KO_*` rule areas. Every other part was placed again (L201 0.9 mm, L402 and L502 by about 29 and 39 mm, most others several mm) and all copper was drawn again. It adds one rule area, `KO_SRN_tap` on F.Cu.
- **Checks:** DRC 0 errors, 0 unconnected, parity 0 (22 warnings); cup fit with `groundup/mechcheck.py`, 0 failed checks. The solver comparison against the hand-routed board is in `groundup/compare/README.md`. Nobody has reviewed the board in KiCad.
- **Made the design on 2026-11-13** (Logan). The renders and plots in `docs/hardware/` and the mechanical model's board data were regenerated from it that day; the hand-routed board's order files moved to `retired/jlc-hand-routed/`. Still to do: a review in KiCad, and the rotations checked in JLC's preview again. Gerbers, drill, BOM and CPL were made together on 2026-11-14 (`jlc/ORDER-NOTES.md`). The reviews and the studies in `docs/analysis/` were not redone for it.
- **Open PR #68** (2026-11-11 cleanup pass of the same board: redrawn signal nets, one width per run) is not merged.

## Board edits before ordering (2026-11-07 and 2026-11-08)

From the 2026-11-07 pre-order review and Logan's answers (PR #64) and his board save of 2026-11-08 (PR #65, commit `36dad0c`, merged as `8dd9eb6`). All on the hand-routed board.

- **UART_TX:** U301 DIO18 (pad 16) to J301 pin 6 on the MCU sheet (2026-11-07), routed by Logan on the board (2026-11-08).
- **Silk labels:** 14 F.SilkS texts at the pack, NTC, cell-tap and WAKE holes (2026-11-08).
- **F.Cu corner fills:** `GND_corner_TL` and `GND_corner_TR` with 14 stitching vias (0.45/0.3), F.Cu copper 37.3 % to 45.1 % against B.Cu's 52.3 % (2026-11-08).
- **Gerbers:** `Monolith_gerbers_JLC.zip` (now in `retired/jlc-hand-routed/`) regenerated from that save; BOM and CPL not touched. DRC 0 errors, 0 unconnected, 16 warnings.
- **Decisions:** R413/R513 stay 11.8k with `EN_ICHG_PIN = 0`; U102 stays BQ294700 (gauge COV 4.25 V); the 12 bottom parts are hand-soldered; SiZ240DT and TPS25751D pre-ordered at JLC. Still open at checkout: the D401/D501 pin-1 check in JLC's preview (`jlc/ORDER-NOTES.md`).

## Part swaps after approval (2026-10-30 and 2026-10-31)

Schematic and JLC BOM changes on the hand-routed board; no footprint or position changed.

- **L402/L502 (2026-10-30):** the 3.1 mm APS0530 at L502 met the cup's corner fillet (final review), so both became 2.0 mm parts on the new footprint `MonolithDev:L_COILMX_MS0520` (same pads as the APS0530): first COILMX MS0520-3R3M, then the same evening ABC EHE05023R3MFB (LCSC C49248023), which JLC stocks.
- **D401/D501 (2026-10-31, PR #52):** TI TVS2200DRVR (C523793, short at JLC) to the Wuxi Maxinmicro TVS2200DRVR, LCSC C55616459. Same pinout and 2 × 2 mm DFN, footprint kept. Its datasheet gives typical values only. Rotated 180° it would short VBUS to GND, hence the pin-1 check at order time.
- **C421/C456/C521/C556 (2026-10-31, PR #54):** KEMET T593V686M035APE070, 68 µF 35 V, 2.0 mm, Mouser only (see *Low-profile bulk* below).
- **Pack wires (2026-10-31):** TE 100G0111-1.00-0 (18 AWG) and 55A0111-28-9 (28 AWG) (see *Pack wire holes* below).

## Routed and approved (2026-10-28 to 2026-10-30)

Placement was finished on 2026-10-28 and routing by Logan on branch `Layout-P0` on 2026-10-29 (`8fd8b74`). The routed board was reviewed several times on 2026-10-30 ([`docs/reviews/2026-10-30-routed-board/`](../../docs/reviews/2026-10-30-routed-board/README.md) and later revisions; see [`docs/reviews/README.md`](../../docs/reviews/README.md)) and approved by Logan the same day (`8081416`, merged in PR #44). The order package (now in `retired/jlc-hand-routed/`) was made from his 22:41 save that night. Changes made during the reviews:

- J1–J4, the single-pin back-cell NTC wire pads that replaced J105 / J106, were renamed J117 (TS2), J118 (TS2 return), J119 (TS3) and J120 (TS3 return) and left out of the BOM.
- U301's antenna keep-out on the board was extended from In1 to In1–In4 and B.Cu, as in the library footprint.
- Logan's routing fixes closed the review's must-fix items (port 1 PACK_P path, port 2 sense taps and ACN keep-out, fuse heater return, VPWR caps).

## How P0 was made

`tools/make_production.py` (re-runnable) copies the dev board's sheets, libraries and project file from `hardware/DevBoard/` and edits them as follows:

- deletes parts by reference, then prunes the wires, labels, junctions, no-connects and power symbols left dangling;
- replaces 0 Ω links with wires;
- adds the production pads.

`tools/tidy_production.py` then tidies the drawings, with no electrical change:

- merges split wires and deletes the wires the link merges left between same-name labels;
- spreads the pogo pads into their own row;
- deletes the headings of removed blocks and renames the rest;
- rewrites every sheet's notes, the root index and the revision log;
- renames the sheets *3V3 Rail* and *MCU*.

`tools/check_netlist.py` then compares the result with the dev board netlist. Every surviving pin must keep its dev net, with only the intended link merges, and every new pad must take the net of the pin it replaces. Result: 956 pins checked, no differences, and 424 parts down to 295. ERC shows the dev board's 8 pin-to-pin warnings plus 3 off-grid notes on the root sheet pins.

`tools/layout_production.py` lays the sheets out: block moves through `hardware/DevBoard/tools/move_region.py`, then `place_fields.py` and `check_overlaps.py` (it should report 0 overlaps).

Run all four in order with KiCad's Python (make, tidy, layout, check):

```bash
"/c/Program Files/KiCad/10.0/bin/python.exe" hardware/Production/tools/make_production.py
```

```bash
"/c/Program Files/KiCad/10.0/bin/python.exe" hardware/Production/tools/tidy_production.py
```

```bash
"/c/Program Files/KiCad/10.0/bin/python.exe" hardware/Production/tools/layout_production.py
```

```bash
"/c/Program Files/KiCad/10.0/bin/python.exe" hardware/Production/tools/check_netlist.py
```

Re-running overwrites the sheets. Once you start editing them by hand in KiCad, stop using the scripts.

## Removed (decided 2026-10-17)

| Sheet | Removed | Why |
|---|---|---|
| Gauge | BT101–BT104 | cell holders; the production pack is welded |
| | J104, D104, D105 | bench supply |
| | R127 | fuse bypass |
| | R114, C109, D102 | DNP options |
| | SW101, R118 | wake button |
| | TP101–TP105, TP107, TP108 | test points |
| Sleep current / 3V3 | U201–U203, JP201/JP202, R202–R206, R208, C201–C205, TP201–TP209 | the whole sleep-current measurement section |
| | R201 (R_MEAS) → wire | PACK_LP is PACK_P now |
| | R207 → wire | link |
| MCU | J302, J303 + their series resistors | UART and spare-GPIO headers |
| | SW301 | reset button |
| | D301, R306, R307 | status LED (none on the product) |
| | R315 (DNP) | unused pull-up |
| | R301, R312 → wires | links |
| | TP302–TP304, TP307–TP309 | test points |
| | | DIO12, DIO18 and DIO20 are now free (no-connect). (2026-11-07: DIO18 now carries UART_TX to J301 pin 6.) |
| USB ×2 | J402 | logic-analyser header |
| | TP402–TP421 | test points |
| | R450/C454, R451/C455 | DNP snubbers; removed before bring-up, by choice |
| | C447 | DNP feed-forward cap |
| | C435 | battery-side bank down to 2 × 22 µF + hybrid: 87 µF effective, hybrid at 63 % of its ripple rating (cap sims 2026-10-17, B2) |
| | R401, R431 → wires | links |
| | R440 → wire | D+/D− become one net, `DPDN_DCP` (rev 2 item 1c) |
| | R448, R449 → wires | BTST links |
| Root | R1–R4 straps | port 1 ADCIN1 is tied to its LDO_3V3; the other ADCIN pins to GND |

## Added or changed

- **PP5V bulk:** C443/C543, the 100 µF polymer, is now a 22 µF 25 V 1206 (CL31A226KAHNNNE, LCSC C12891, the same part as C441). This leaves three 22 µF parts, about 33 µF effective, and saves about 43 mm² per port.
    - Each port's PP5V comes from its own TPS62933, so the USB PD cSrcBulk minimum (10 µF, dedicated supply) applies. The 120 µF cSrcBulkShared in the TPS25751 table is for a shared supply (checked 2026-10-17, `docs/devboard/cap-reduction-sims-2026-10-17.md`).
    - The estimated 0.5 → 3 A step undershoot is about 190 mV against a 250 mV budget. Measure it on the dev board with C443 removed. (The dev board was never built, 2026-10-18: measure it on P0.)
- **Pack wires:**
    - J108 PACK− (CELL_N) and J112 PACK+ (CELL_P_RAW): 18 AWG wires (TE 100G0111-1.00-0, up to 1.8 mm OD) in Ø1.5 mm plated holes (since 2026-10-24, *Pack wire holes* below);
    - J109–J111 (CELL1–CELL3) and J115 / J116 (1N / 4P Kelvin): 28 AWG sense wires (TE 55A0111-28-9) in Ø0.8 mm plated holes (since 2026-10-24, *Pack wire holes* below);
    - J105 / J106: back-cell (C2 / C3) NTC wire pads (replaced on 2026-10-30 by the single-pin pads J117 / J118 for TS2 and J119 / J120 for TS3, see *Routed and approved* above). The front cells' NTCs are SMD since 2026-10-28: TH101 (C1, TS1) and TH104 (C4, TS4), 0402s on B.Cu at |y| 15.5 mm, z 29 mm (KiCad (84.5, 112.48) / (115.5, 112.48), 90°, locked; `sb_ntc_smd()`), in a notch at the outer edge of each gap-filler keep-out, under the gel (`research_notes/Pack thermal BAK 65E/smd-ntc.md`). They replace J102 / J107 and the wired beads.
- **Gauge access:** TP110 SMBC, TP111 SMBD, TP112 GND, 1.5 mm pogo pads in a row (replace the EV2400 header J103). Later replaced by the J302 Tag-Connect (see below).
- **SWD:** J301 is a Tag-Connect TC2030-NL footprint (VCC, SWDIO, NRST, SWCLK, GND; SWO not connected). Use an XDS110 with a TC2030-CTX cable.
- **Factory test pads (1.5 mm):** TP106 PACK_P, TP109 GND, TP301 3V3, TP401/TP501 VBUS.

## Loss cuts 1–3 (adopted 2026-10-23, drawn 2026-10-28)

The board-side loss cuts from `docs/spec.md` (*Decided: the four loss cuts*). Port 1 references; port 2 is 5xx.

| Cut | Parts | Change |
|---|---|---|
| 1. Protection FETs | Q101, Q102 | AGM404AP1 (3.3 × 3.3) → Infineon BSC007N04LS6 (LCSC C534274), 0.70 mΩ, TDSON-8 FL 5 × 6. Footprint `Infineon_PG-TDSON-8_6.15x5.15mm_D5-8`: KiCad's PG-TDSON-8 with the drain leads numbered 5–8 to match the symbol (`tdson_footprint()`). Check it against the datasheet's footprint drawing before fab |
| 2. 9 V gate drive | U406, C457, C458, R452–R455, D410, D411, Q409 | See below |
| 3. Inductor + 500 kHz | L401, R412 | Coilcraft XGL7030-332MEC 3.3 µH on the APS0730 pads (consigned); R412 40.2k → 49.9k (598 → ~500 kHz). R412's LCSC code (0201WMF4992TEE) is still to look up (2026-10-30: 0201WMF4992TEE is the MPN; LCSC C7343965 is in the JLC BOM only, not in the schematic) |

**9 V gate drive, per port** (`add_gate_drive()`, symbol in `tools/tps7a4101.py`), in the free area right of the BQ25756 controller block:

- U406 TPS7A4101DGNR (LCSC C111739, HVSSOP-8 PowerPAD) runs from PACK_P. C457 1 µF 50 V in, C458 22 µF 25 V 0805 out (the LDO needs ≥ 4.7 µF; about 8 µF is left at 9.6 V). R452 40.2k / R453 5.6k set 1.173 × (1 + 40.2/5.6) ≈ 9.6 V.
- D411 (LRB520S-40) ORs it onto DRV_SUP at about 9.3 V. D410 (LRB520S-40) replaces R420 (10 Ω REGN → DRV_SUP), so with U406 off DRV_SUP is REGN − VF, TI's standard drive, and a dead pack still charges. The output diode is needed because the TPS7A41's OUT may not sit more than 0.3 V above IN.
- EN: R454 (100k) from REGN, pulled low by Q409 (AO3400A) unless TPS25751 GPIO6 (net DRV9_OFF) is low. R455 (100k) pulls Q409's gate up to the port's LDO_3V3, so GPIO6 Hi-Z (reset, no configuration) or high means 9 V off. GPIO6 leaves the unused-GPIO GND rail (`free_gpio6()`); its wire crosses the rail without a junction.
- Firmware: GPIO6 as an output with initial value high; `GPsl` turns the 9 V on, `GPsh` off. On only while that converter switches, for contracts ≥ 45 W and with PACK_P ≥ 10 V (the TPS7A41's EN may not sit more than 0.3 V above IN either). With REGN down, EN is low, so DRV_SUP is never driven while the BQ25756 is off (bq25756.pdf 6.3.3.2).
- C411 4.7 µF 10 V 0402 → 4.7 µF 25 V 0805 (CL21A475KAQNNNE, C1779).

The committed sheets were updated by calling these functions (`edit_symbols`, `add_gate_drive`, `tdson_footprint`, tidy's notes) on the existing files, because KiCad can't be installed in the cloud session that made the change; a full `make_production.py` run produces the same result. Connectivity was checked by a script that compares every pin's net before and after (only the intended changes); **ERC, check_netlist.py and Update PCB from Schematic are still to run in KiCad.**

## Passive downsizing (2026-10-17)

Production may use JLC extended parts and 0201 parts. 0201 is used only where both of a part's nets stay at or below 5.5 V. The swaps are in `DOWNSIZE` in `tools/make_production.py`, and each part was checked for rating and JLC stock the same day.

Courtyard area went from **2,653 to 2,221 mm²** for all placed parts (−16 %). Passives alone went from about 1,570 to 1,170 mm² (−25 %).

| Change | Parts (port 1 shown, port 2 = 5xx) | Saved |
|---|---|---|
| Charger inductor 10×10 → Coilank APS0730M2R2F (7.8×7.6×3.1 mm) | L401/L501 | 162 mm² |
| 0603 resistors → 0402 | R110, R112, R117, R410, R413–R416, R420, R433, R444–R447 | ~60 mm² |
| Low-voltage R/C 0402 → 0201 | pull-ups and pull-downs, SMBus series R, FSW, MCU and LDO_3V3 decoupling | ~30 mm² |
| Sense resistors: RAC 2010 → 0805 0.5 W, RBAT 2010 → 1206 1 W, gauge shunt 2512 → 1206 1 W 75 ppm | R424, R427, RS101 | ~58 mm² |
| Cell filter resistors 1206 → 0402 (with a welded pack, no cell can be reversed in an open holder) | R101–R104 | 34 mm² |
| BAT54WS SOD-323 → Nexperia BAT54L SOD-882 | D101, D406–D409 | ~37 mm² |
| REGN/DRV_SUP, sense filter and soft-start caps 0603 → 0402 | C410, C411, C414, C417, C439 | ~13 mm² |
| NTC 0603 → 0402 (NCP15XH103F03RC: same 3380/3435 K curve, so the TS thresholds don't move) | TH401 | 3 mm² |

**Checked and kept:**

- **Bulk polymers C421/C432.** No smaller 100 µF 35 V polymer is stocked. The only smaller 25 V option is a polymer tantalum, rated for up to 250 µA leakage, which would wreck the sleep budget on PACK_P. (Superseded on 2026-10-18 by *Low-profile bulk*.)
- **TPS25751 VIN_3V3, LDO_3V3 and PP5V caps.** Their datasheet minimums after derating don't fit a 0402.
- **50 V 1206s on 5V_IN and VBUS.** DC bias at 16.8–20 V would take them under the TPS62933 and TPS25751 needs.
- **C207**, the TPS62177 output cap.
- **The RF match parts**, kept at 0402 so they can be retuned.

**Inductor trade-off:** the APS0730 costs $0.56 against about $8.50 for the Coilcraft XAL7070-222. In return it runs hotter: about 1.6 W DCR loss at the worst case (reverse 20 V 5 A from a 10 V pack), against about 1.0 W for the old part. It also drops to about 1.7 µH at the 12 A peak. Measure its temperature on the dev board before committing to it. The XAL7070-222 fits the same space if it runs too hot.

## Gate drive and shared battery-side bulk (2026-10-17)

- **Gate resistors and diodes removed.** R444–R447 are now copper, and D406–D409 are gone (both ports): HIDRV/LODRV drive the FET gates directly. The dev board fits 10 Ω gate resistors, so measure SW1/SW2 ringing there with them bridged before relying on this.
- **One shared battery-side hybrid.** Both chargers' battery sides, both TPS62933 inputs and the pack all sit on one PACK_P bus, so `tools/pack_bus_sims.py` models them as one network. Each port's MLCCs sit behind its 5 mΩ RBAT, and the shared bulk sits between the two power stages. The model runs both chargers and both bucks together: single-port worst cases, both ports sourcing, pass-through, and a buck plus a charger.

| Option | Battery-side effective C (worst, 16.8 V) | Worst part | Ripple | Damping | Area |
|---|---|---|---|---|---|
| Before: 2 × 22 µF + hybrid + 2 × 10 µF 50 V, per port | 185 µF | 47 % | 80 mV | 20.3 dB | 217 mm² |
| One shared hybrid, rest unchanged | 105 µF | 28 % | 148 mV | 20.2 dB | 151 mm² |
| **Applied: one shared hybrid, 2 × 22 µF + 1 × 10 µF 50 V per port** | **99 µF** | **44 %** | **232 mV** | **20.2 dB** | **130 mm²** |
| As applied, but 1 × 22 µF per port | 92.5 µF | 55 % | 267 mV | 20.0 dB | 109 mm² |
| No hybrid at all | 25 µF (below the 80 µF minimum) | 27 % | 143 mV | 14.5 dB | 84 mm² |

The BQ25756 needs C_OUT ≥ 80 µF after derating (datasheet sec. 5.3). Each charger sees the whole bus through its RBAT, so one hybrid has to stay.

- **Removed:** C432/C532, the per-port hybrids, and C445/C545, the second TPS62933 input caps.
- **Added:** C208, a 100 µF 25 V hybrid (EEH-ZA1E101XP) on the 3V3 Rail sheet. Place it between the two power stages on PACK_P, next to both RBAT pads.
- **USB sides:** these can't share bulk, because each port has its own VBUS/PPHV, so C421/C521 stay. C427 is still on hold for bring-up. (Both superseded on 2026-10-18 by *Low-profile bulk*: C208 became six MLCCs, C421 became two polymer tantalums, and C427 is now required.)

**Totals:** 276 parts (262 placed), and courtyard area is now **2,104 mm²**, down from 2,653 mm² before any downsizing (−21 %).

## Liquid detection removed (2026-10-17)

The production ports have IP68 connectors and a potted board, so liquid detection is dropped. Port 1 is listed; port 2's 5xx parts are the same.

- **Removed:** Q403–Q406 (SBU pull FETs), R436–R439 and R442/R443.
- **TPS25751 GPIO4–GPIO7:** tied to GND, as its datasheet says for unused GPIOs. Configure them as unused in the TPS25751 configuration, never as outputs.
- **TPD4S201 system-side SBU pins:** left as no-connects. Grounding them would short a cable's SBU lines whenever the SBU switch is on.
- **Kept:** the TPD4S201 itself, for CC and SBU overvoltage and ESD protection, and its fault output R441 → GPIO3.
- **ERC:** shows 8 more of the expected "GPIO tied to GND" pin-to-pin warnings, 16 in total.

Parts: 256.

**Checked and not applied: dual FETs for the chargers (packaging option 4).**

- **40 V half-bridges at JLC** come only in 5×6 mm (Infineon IAUC60N04S6N050), the same area as two 3.3×3.3 singles.
- **3.3×3.3 half-bridges** are 30 V only (SiZ340). That's too little with 20 V VBUS, the 22.5 V OVP and the 28 V TVS clamp, now that there are no gate resistors.
- **3×3 duals with independent FETs** could pair only the two low sides, Q407 + Q408: their sources share GND, and the two never carry heavy current at the same time. The high sides can't share: about 2 W in one package at the worst case.
- **The dual parts on offer don't qualify:** the genuine Vishay SiSB46DN is out of stock and has 15.8 mΩ at 4.5 V (today's part: 10 mΩ). The stocked "SiSB46DN-HXY" clone lists specs the original doesn't have. Other duals are 13–22 mΩ.
- **Not worth it:** the gain would be only about 31 mm² for both ports, so the four singles per port stay.

## Board: stack-up, outline and pour plan (2026-10-17)

`tools/make_board.py` writes the stack-up, layer table, thickness and outline into `Monolith.kicad_pcb`. It patches an existing board without touching footprints. Once the board has copper it refuses, unless `--keep-copper` is passed, which leaves every trace where it is. It also copies the dev board's custom DRC rules to `Monolith.kicad_dru`.

**Outline:** since 2026-10-18, the side board of the one-piece tray. The details are in *Side outline and 1.6 mm board* below. The 40.5 mm and then 45.5 mm top-cap outlines that came before it are kept below as history.

- `monolith_bottom_pcb.dxf` (removed 2026-10-29, in git at `5cf521e`) was the old 43.3 mm bottom end board with the 8 mm vent, not this board.

**Stack-up:** 6 layers, **1.6 mm** (2026-10-18, for cost; it was 0.8 mm), 2 oz outer / 0.5 oz inner, ENIG. Vias are filled and capped, JLC's default on 6+ layers, so via-in-pad is free. No net here needs controlled impedance, so the split below is a symmetric approximation. Replace it with JLC's stack at order time.

| Layer | Copper | Dielectric below | Role | Never |
|---|---|---|---|---|
| F.Cu | 70 µm | prepreg 0.20 | outer face: parts that make heat (power stages, inductors, BQ25756s), facing the gap pad and the aluminium cover; one pour per power net in its block; GND fill elsewhere, stitched to In1 every 3–5 mm | sense pairs through power pours |
| In1.Cu | 17.5 µm | core 0.30 | **solid GND**: return for F.Cu and both hot loops | any trace, split or other-net island |
| In2.Cu | 17.5 µm | prepreg 0.39 | signals, vertical only: Kelvin pairs, cell taps, FB/ILIM, I2C; 3V3 as a local pour | high current, switch nodes |
| In3.Cu | 17.5 µm | core 0.30 | signals, horizontal only: cross-board nets, gate-drive pairs that must leave F.Cu; PP5V local pours | high current |
| In4.Cu | 17.5 µm | prepreg 0.20 | **solid GND**: return for B.Cu | any trace, split or other-net island |
| B.Cu | 70 µm | | cell side, against the insulator: only low parts in the free strips (see the side outline section), ideally none; mirror of F.Cu high-current pours where no parts sit, stitched; GND fill | switch-node copper |

- **Second ground:** the gauge's VSS (CELL_N) is local fill on F.Cu/B.Cu around U101, joined to GND only through RS101. It never goes on In1/In4.
- **Antenna:** keep-out on every layer under the CC2340 antenna end, with solid ground either side at a board edge.
- **Board thickness:** 1.6 mm, for cost. JLC's multilayer minimum at 1.6 mm is a 0.15 mm hole on a 0.25 mm via, with a surcharge below a 0.2 mm hole or under a 0.45 mm via. The 0.1 mm / 0.2 mm via option needs a board of 1 mm or less, so it's gone. The project minimum (0.35/0.2 mm) is still inside JLC's limits (the TPD2S300's 0.15 mm via-in-pad is gone: U405/U505 are TPD6S300s since 2026-10-18) ([JLC capabilities](https://jlcpcb.com/capabilities/pcb-capabilities), checked 2026-10-18).
- **Via rules (`Monolith.kicad_pro`):**
    - default 0.45/0.3 mm, HighCurrent 0.8/0.4 mm;
    - minimum lowered to **0.35/0.2 mm** for fan-out (holes under 0.3 mm may carry a JLC surcharge: check the quote);
    - tracks 0.15/0.15 mm (JLC 2 oz multilayer); copper to edge 0.2 mm.
- **USB-C:** J401/J501 are the **TYPE-C 16PCB1.6 IP68** (C55629729), the 1.6 mm board version, since 2026-10-18 (before that, the 16PCB0.8, C55629727). The land pattern is identical, so only the footprint name and part fields changed, in the schematic, on the board and in `tools/make_production.py`.

## Side outline and 1.6 mm board (2026-10-18)

The board moved from the top cap to one side of the cells, in a one-piece printed tray (`hardware/mechanical/`, see the root README). The tray was replaced by the cup on 2026-10-21 (*Enclosure: the cup* below); the outline stayed. The board thickness went to 1.6 mm, for cost.

- **Outline:** 43.2 × 74.35 mm, about 3,164 mm² per side.
    - The bottom corners are notched 5.0 × 4.8 mm around the cover-screw bosses (on the wedge since 2026-10-21; they were tray pillars).
    - The outline comes from `hardware/mechanical/monolith_shell.py` (`sb_*`), which `tools/make_board.py` imports, so the tray and the board can't drift apart. The same outline is in `hardware/mechanical/monolith_side_pcb.dxf`.
    - It is centred at (100, 100). KiCad x is across the pack (left = the C1 / PACK- side), and KiCad y runs down the pack, with the port end at the top.
- **Ports:** J501 (USB2) at x = 93.5 and J401 (USB1) at x = 106.5, on the top edge (y = 62.82), rotated 180°, locked. The outline leaves the two 10.2 mm notch gaps.
- **Faces:**
    - F.Cu faces the aluminium cover through a gap pad: up to 3.2 mm of part height (the APS0730 inductor is 3.1 mm).
    - B.Cu faces the cells through a 0.3 mm insulator. Along the two cell tangent lines (8–13 mm from centre) there is only 0.3–0.8 mm, which the insulator mostly fills. There are 3 mm or more within 4 mm of centre and beyond 18 mm from it.
- **Pack connections** become nickel-tab pads instead of the 16 AWG holes:
    - PACK- (C1 side) and PACK+ (C4 side) at the bottom edge, within 16 mm of centre, clear of the notches;
    - CELL2 at the bottom; CELL1 and CELL3 at the top.
    - The cell order and the assembly steps are in the assembly doc.
- **Vent:** keep a Ø7 mm circle free of tall parts and gap pad, centred 12 mm above the tray bottom (shown on the DXF's `VENT_KEEPOUT` layer). Gone since 2026-10-28: the board needs no vent keep-out. (Since 2026-10-31 the vent is a 12 mm ePTFE patch on the cap under the bottom bumper, with no hole in the cup or label and no board change.)
- **Still to do:**
    - Placement: every part except J401/J501 still sits where it was.
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
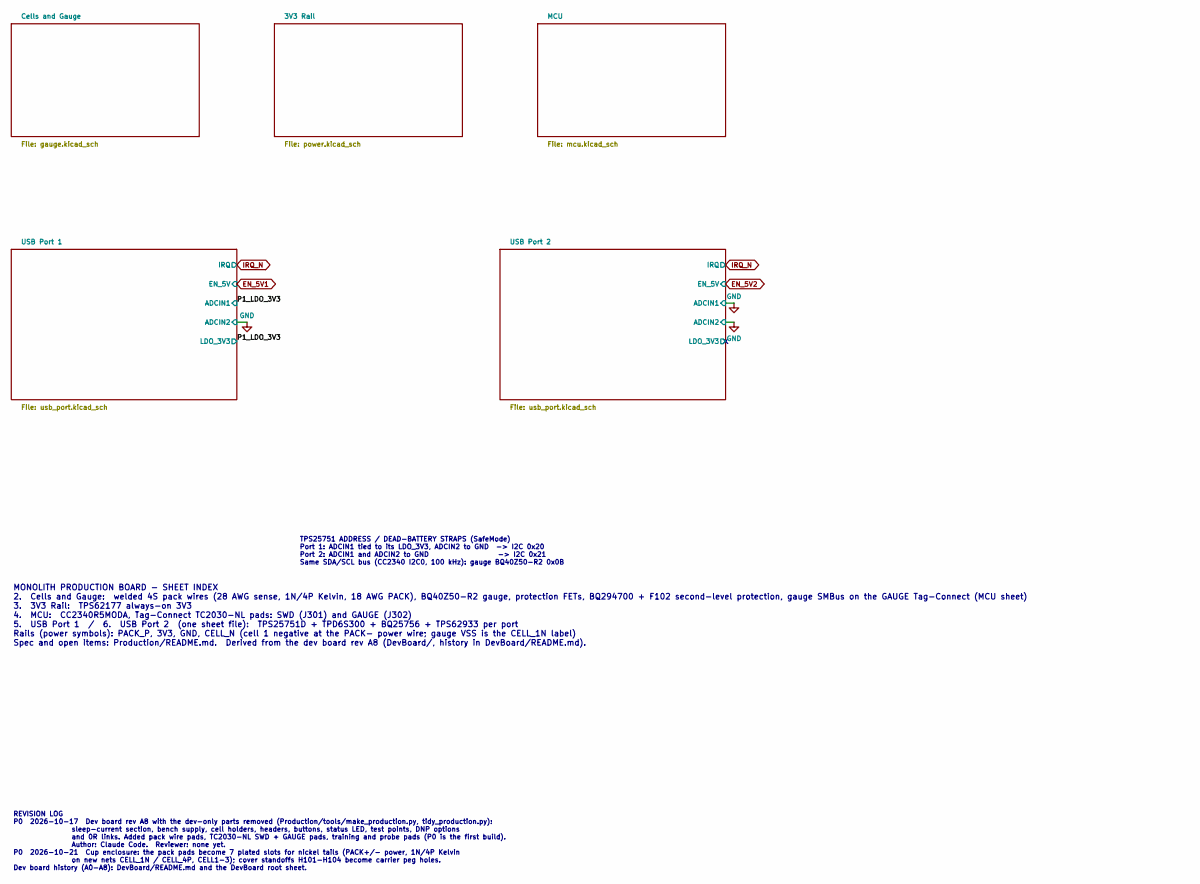
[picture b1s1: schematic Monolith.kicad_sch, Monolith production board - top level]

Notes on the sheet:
MONOLITH PRODUCTION BOARD - SHEET INDEX 2. Cells and Gauge: welded 4S pack wires (28 AWG sense, 1N/4P Kelvin, 18 AWG PACK), BQ40Z50-R2 gauge, protection FETs, BQ294700 + F102 second-level protection, gauge SMBus on the GAUGE Tag-Connect (MCU sheet) 3. 3V3 Rail: TPS62177 always-on 3V3 4. MCU: CC2340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
REVISION LOG P0 2026-10-17 Dev board rev A8 with the dev-only parts removed (Production/tools/make_production.py, tidy_production.py): sleep-current section, bench supply, cell holders, headers, buttons, status LED, test points, DNP options and 0R links. Added pack wire pads, TC2030-NL SWD + GAUGE 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
TPS25751 ADDRESS / DEAD-BATTERY STRAPS (SafeMode) Port 1: ADCIN1 tied to its LDO_3V3, ADCIN2 to GND -> I2C 0x20 Port 2: ADCIN1 and ADCIN2 to GND -> I2C 0x21 Same SDA/SCL bus (CC2340 I2C0, 100 kHz): gauge BQ40Z50-R2 0x0B

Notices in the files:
parts and their libraries:
License: Apache-2.0
